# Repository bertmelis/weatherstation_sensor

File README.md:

# Weather station (sensor)

This repo contains the files the sensor of my little weather station. It is built using a battery powered ATtiny85, a BME280 and a nRF24.

**Work in progress!**

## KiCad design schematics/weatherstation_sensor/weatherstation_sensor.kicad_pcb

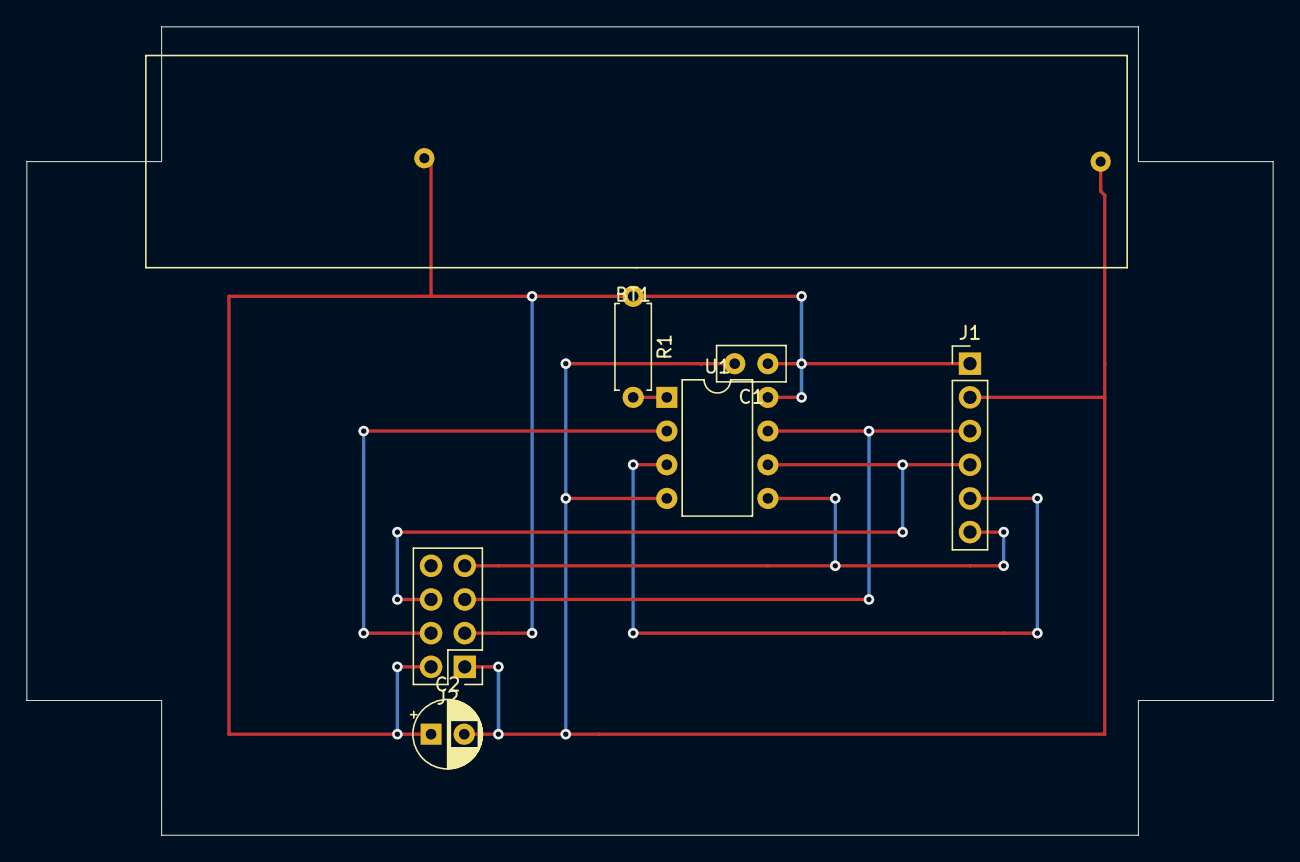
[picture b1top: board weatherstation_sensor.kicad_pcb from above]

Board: 2 copper layers, 94.0 x 61.0 mm, 7 parts (0 on the bottom side), 8 nets.

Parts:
BT1: 3.3V; LiFePO4wered_USB
C1: 100nF; C_Disc_D5.0mm_W2.5mm_P2.50mm
C2: 10µF; CP_Radial_D5.0mm_P2.50mm
J1: CONN_BME280; PinHeader_1x06_P2.54mm_Vertical
J2: CONN_NRF24; PinHeader_2x04_P2.54mm_Vertical
R1: 10k; R_Axial_DIN0207_L6.3mm_D2.5mm_P7.62mm_Horizontal
U1: ATtiny85V-10PU; DIP-8_W7.62mm

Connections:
+3V3: BT1.1, C1.1, C2.1, J1.1, J2.2, J2.3, R1.1, U1.8
CS_BME280: J1.5, U1.3
CS_NRF24: J2.4, U1.2
GND: BT1.2, C1.2, C2.2, J1.2, J2.1, U1.4
unnamed: R1.2, U1.1
RX: J1.4, J2.6, U1.6
SPI_CLK: J1.3, J2.5, U1.7
SPI_MISO: J1.6, J2.7, U1.5

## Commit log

2020-02-27 Fix humidity sensing
    - BME280: fix wrong readout of trimming params
    - BME280: var initialization
    - BME280: reorder setup
    - MAIN: implement humid/press sensing
2020-02-27 don't use bootloader
2020-03-17 Add schematics
    and cosmetic in code
2020-03-30 Allow better range
    + use optiboot by default
